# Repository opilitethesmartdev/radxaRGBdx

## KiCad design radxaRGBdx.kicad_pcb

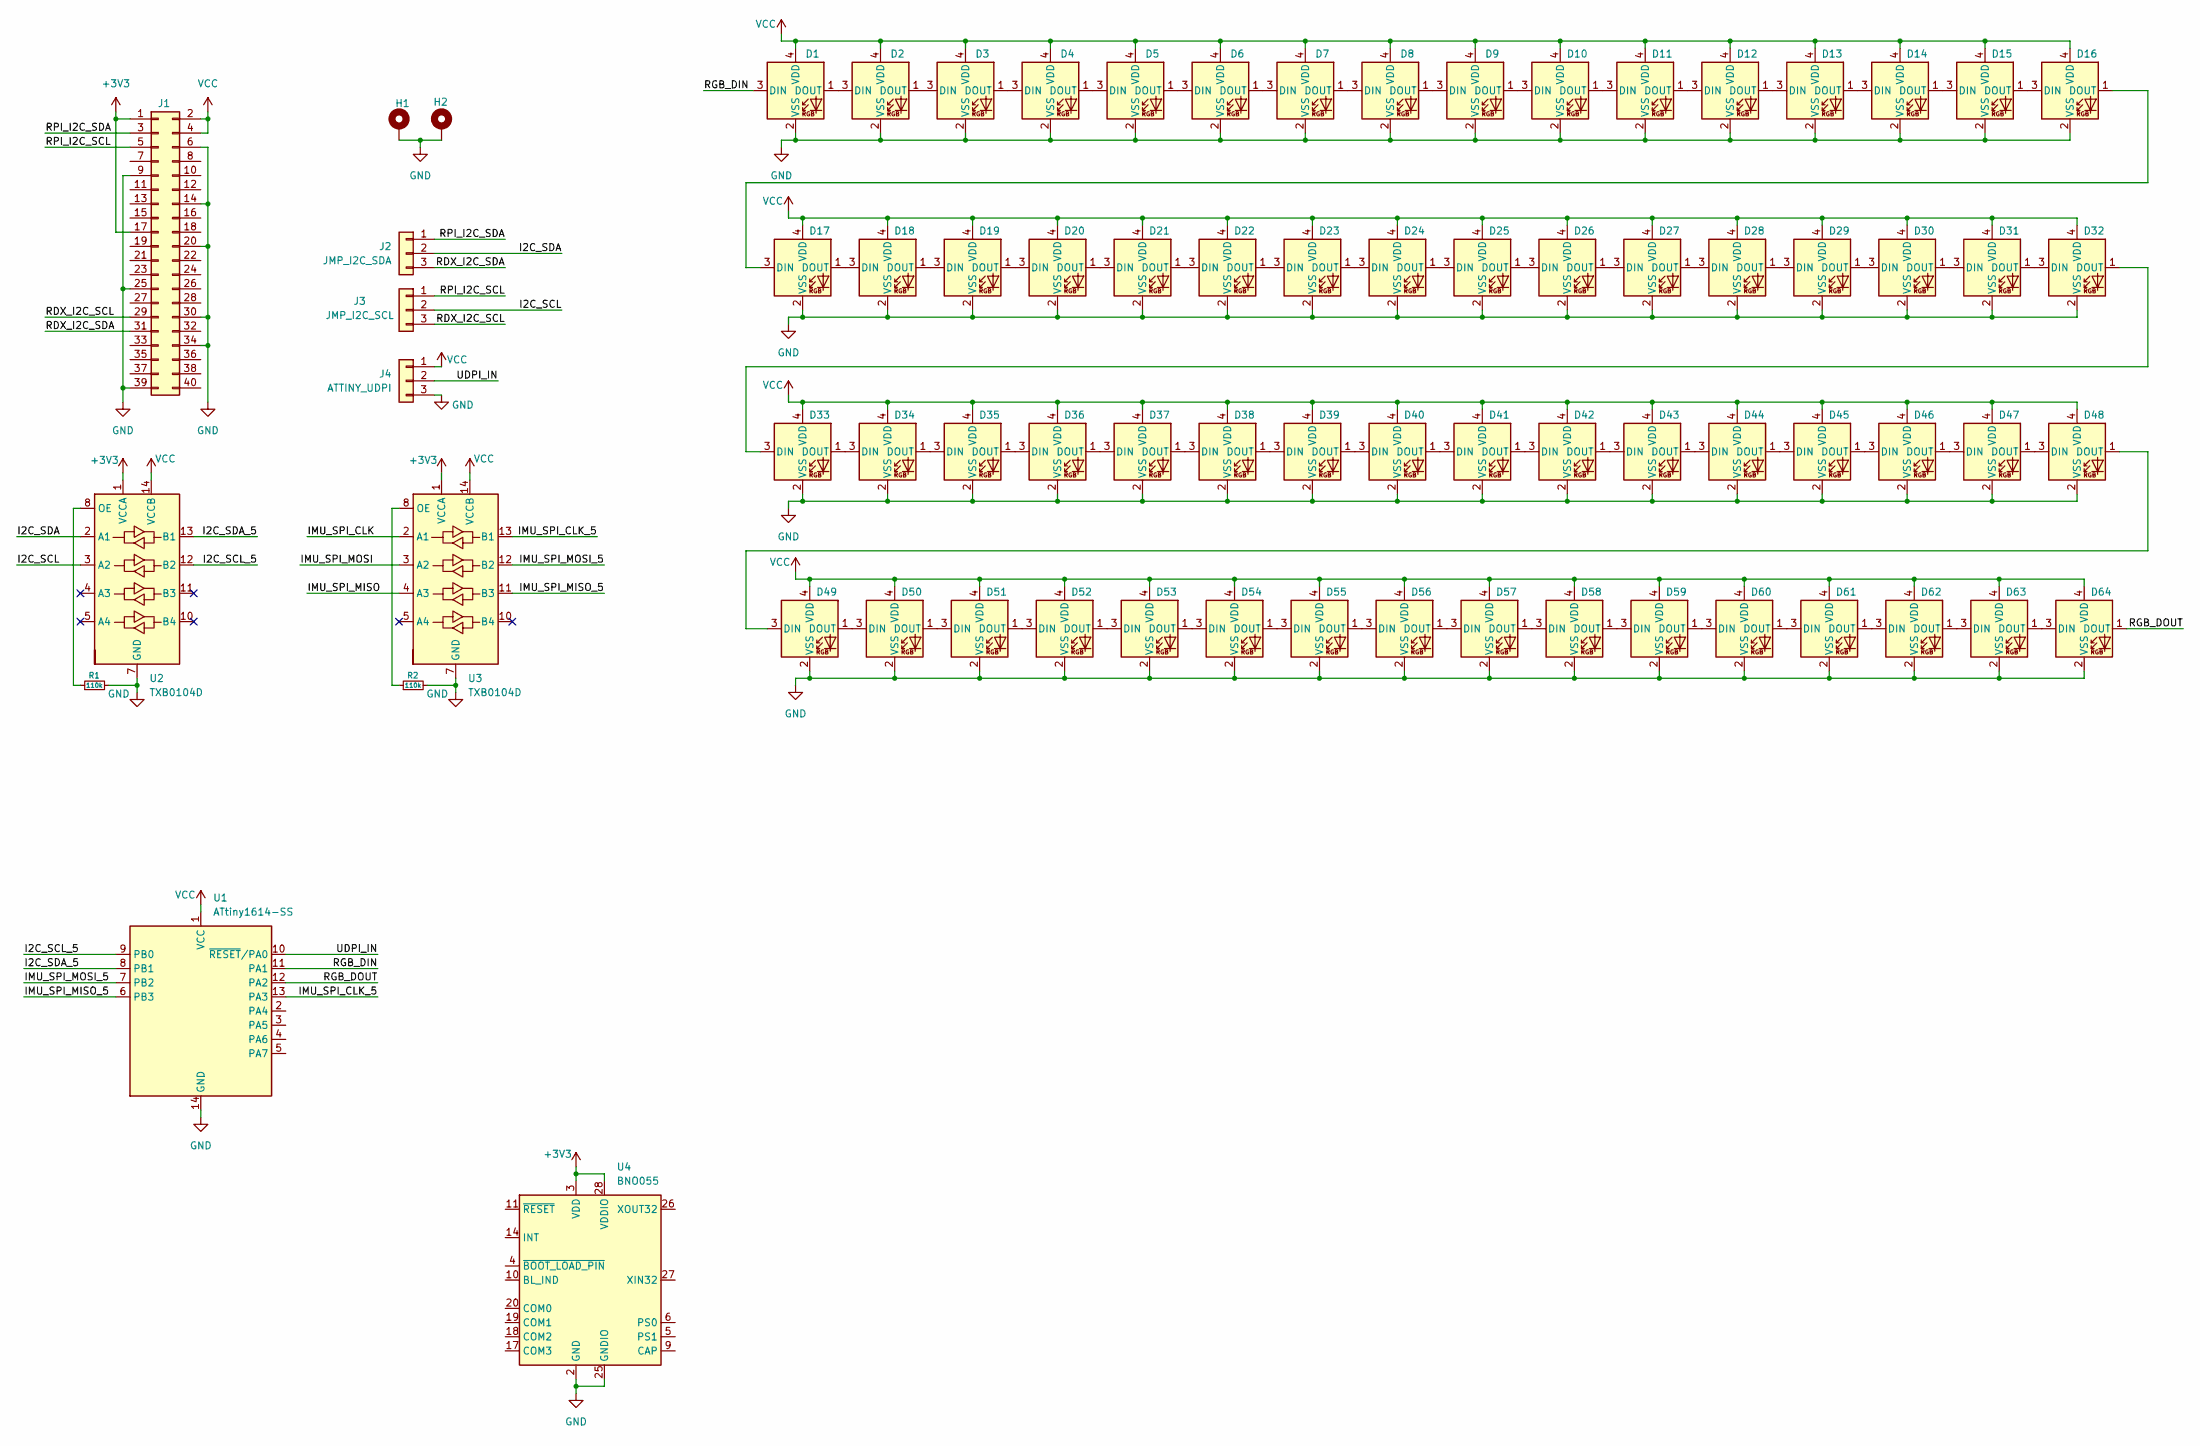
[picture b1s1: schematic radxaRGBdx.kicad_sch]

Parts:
D1, D2, D3, D4, D5, D6, D7, D8, D9, D10, D11, D12, D13, D14, D15, D16, D17, D18, D19, D20, D21, D22, D23, D24, D25, D26, D27, D28, D29, D30, D31, D32, D33, D34, D35, D36, D37, D38, D39, D40, D41, D42, D43, D44, D45, D46, D47, D48, D49, D50, D51, D52, D53, D54, D55, D56, D57, D58, D59, D60, D61, D62, D63, D64: WS2812B-2020; LED_WS2812B-2020_PLCC4_2.0x2.0mm
H1, H2: MountingHole_Pad; MountingHole_3.2mm_M3_DIN965_Pad
J1: Conn_02x20_Odd_Even; PinSocket_2x20_P2.54mm_Vertical
J2: JMP_I2C_SDA; PinHeader_1x03_P1.27mm_Vertical
J3: JMP_I2C_SCL; PinHeader_1x03_P1.27mm_Vertical
J4: ATTINY_UDPI; PinHeader_1x03_P2.54mm_Vertical
R1, R2: 110k; R_1206_3216Metric_Pad1.42x1.75mm_HandSolder
U1: ATtiny1614-SS; SOIC-14_3.9x8.7mm_P1.27mm
U2, U3: TXB0104D; SOIC-14_3.9x8.7mm_P1.27mm
U4: BNO055; LGA-28_5.2x3.8mm_P0.5mm

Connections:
+3V3: J1.1, J1.17, U2.1 (VCCA), U3.1 (VCCA), U4.3 (VDD), U4.28 (VDDIO)
/I2C_SCL: J3.2, U2.3 (A2)
/I2C_SCL_5: U1.9 (PB0), U2.12 (B2)
/I2C_SDA: J2.2, U2.2 (A1)
/I2C_SDA_5: U1.8 (PB1), U2.13 (B1)
/IMU_SPI_CLK: U3.2 (A1)
/IMU_SPI_CLK_5: U1.13 (PA3), U3.13 (B1)
/IMU_SPI_MISO: U3.4 (A3)
/IMU_SPI_MISO_5: U1.6 (PB3), U3.11 (B3)
/IMU_SPI_MOSI: U3.3 (A2)
/IMU_SPI_MOSI_5: U1.7 (PB2), U3.12 (B2)
/RDX_I2C_SCL: J1.29, J3.3
/RDX_I2C_SDA: J1.31, J2.3
/RGB_DIN: D1.3 (DIN), U1.11 (PA1)
/RGB_DOUT: D64.1 (DOUT), U1.12 (PA2)
/RPI_I2C_SCL: J1.5, J3.1
/RPI_I2C_SDA: J1.3, J2.1
/UDPI_IN: J4.2, U1.10 (~RESET/PA0)
GND: D1.2 (VSS), D2.2 (VSS), D3.2 (VSS), D4.2 (VSS), D5.2 (VSS), D6.2 (VSS), D7.2 (VSS), D8.2 (VSS), D9.2 (VSS), D10.2 (VSS), D11.2 (VSS), D12.2 (VSS), D13.2 (VSS), D14.2 (VSS), D15.2 (VSS), D16.2 (VSS), D17.2 (VSS), D18.2 (VSS), D19.2 (VSS), D20.2 (VSS), D21.2 (VSS), D22.2 (VSS), D23.2 (VSS), D24.2 (VSS), D25.2 (VSS), D26.2 (VSS), D27.2 (VSS), D28.2 (VSS), D29.2 (VSS), D30.2 (VSS), D31.2 (VSS), D32.2 (VSS), D33.2 (VSS), D34.2 (VSS), D35.2 (VSS), D36.2 (VSS), D37.2 (VSS), D38.2 (VSS), D39.2 (VSS), D40.2 (VSS), D41.2 (VSS), D42.2 (VSS), D43.2 (VSS), D44.2 (VSS), D45.2 (VSS), D46.2 (VSS), D47.2 (VSS), D48.2 (VSS), D49.2 (VSS), D50.2 (VSS), D51.2 (VSS), D52.2 (VSS), D53.2 (VSS), D54.2 (VSS), D55.2 (VSS), D56.2 (VSS), D57.2 (VSS), D58.2 (VSS), D59.2 (VSS), D60.2 (VSS), D61.2 (VSS), D62.2 (VSS), D63.2 (VSS), D64.2 (VSS), H1.1 (1_1), H2.1 (1_1), J1.6, J1.9, J1.14, J1.20, J1.25, J1.30, J1.34, J1.39, J4.3, R1.2, R2.2, U1.14 (GND), U2.7 (GND), U3.7 (GND), U4.2 (GND), U4.25 (GNDIO)
unnamed: D1.1 (DOUT), D2.3 (DIN)
unnamed: D2.1 (DOUT), D3.3 (DIN)
unnamed: D3.1 (DOUT), D4.3 (DIN)
unnamed: D4.1 (DOUT), D5.3 (DIN)
unnamed: D5.1 (DOUT), D6.3 (DIN)
unnamed: D6.1 (DOUT), D7.3 (DIN)
unnamed: D7.1 (DOUT), D8.3 (DIN)
unnamed: D8.1 (DOUT), D9.3 (DIN)
unnamed: D9.1 (DOUT), D10.3 (DIN)
unnamed: D10.1 (DOUT), D11.3 (DIN)
unnamed: D11.1 (DOUT), D12.3 (DIN)
unnamed: D12.1 (DOUT), D13.3 (DIN)
unnamed: D13.1 (DOUT), D14.3 (DIN)
unnamed: D14.1 (DOUT), D15.3 (DIN)
unnamed: D15.1 (DOUT), D16.3 (DIN)
unnamed: D16.1 (DOUT), D17.3 (DIN)
unnamed: D17.1 (DOUT), D18.3 (DIN)
unnamed: D18.1 (DOUT), D19.3 (DIN)
unnamed: D19.1 (DOUT), D20.3 (DIN)
unnamed: D20.1 (DOUT), D21.3 (DIN)
unnamed: D21.1 (DOUT), D22.3 (DIN)
unnamed: D22.1 (DOUT), D23.3 (DIN)
unnamed: D23.1 (DOUT), D24.3 (DIN)
unnamed: D24.1 (DOUT), D25.3 (DIN)
unnamed: D25.1 (DOUT), D26.3 (DIN)
unnamed: D26.1 (DOUT), D27.3 (DIN)
unnamed: D27.1 (DOUT), D28.3 (DIN)
unnamed: D28.1 (DOUT), D29.3 (DIN)
unnamed: D29.1 (DOUT), D30.3 (DIN)
unnamed: D30.1 (DOUT), D31.3 (DIN)
unnamed: D31.1 (DOUT), D32.3 (DIN)
unnamed: D32.1 (DOUT), D33.3 (DIN)
unnamed: D33.1 (DOUT), D34.3 (DIN)
unnamed: D34.1 (DOUT), D35.3 (DIN)
unnamed: D35.1 (DOUT), D36.3 (DIN)
unnamed: D36.1 (DOUT), D37.3 (DIN)
unnamed: D37.1 (DOUT), D38.3 (DIN)
unnamed: D38.1 (DOUT), D39.3 (DIN)
unnamed: D39.1 (DOUT), D40.3 (DIN)
unnamed: D40.1 (DOUT), D41.3 (DIN)
unnamed: D41.1 (DOUT), D42.3 (DIN)
unnamed: D42.1 (DOUT), D43.3 (DIN)
unnamed: D43.1 (DOUT), D44.3 (DIN)
unnamed: D44.1 (DOUT), D45.3 (DIN)
unnamed: D45.1 (DOUT), D46.3 (DIN)
unnamed: D46.1 (DOUT), D47.3 (DIN)
unnamed: D47.1 (DOUT), D48.3 (DIN)
unnamed: D48.1 (DOUT), D49.3 (DIN)
unnamed: D49.1 (DOUT), D50.3 (DIN)
unnamed: D50.1 (DOUT), D51.3 (DIN)
unnamed: D51.1 (DOUT), D52.3 (DIN)
unnamed: D52.1 (DOUT), D53.3 (DIN)
unnamed: D53.1 (DOUT), D54.3 (DIN)
unnamed: D54.1 (DOUT), D55.3 (DIN)
unnamed: D55.1 (DOUT), D56.3 (DIN)
unnamed: D56.1 (DOUT), D57.3 (DIN)
unnamed: D57.1 (DOUT), D58.3 (DIN)
unnamed: D58.1 (DOUT), D59.3 (DIN)
unnamed: D59.1 (DOUT), D60.3 (DIN)
unnamed: D60.1 (DOUT), D61.3 (DIN)
unnamed: D61.1 (DOUT), D62.3 (DIN)
unnamed: D62.1 (DOUT), D63.3 (DIN)
unnamed: D63.1 (DOUT), D64.3 (DIN)
unnamed: R1.1, U2.8 (OE)
unnamed: R2.1, U3.8 (OE)
VCC: D1.4 (VDD), D2.4 (VDD), D3.4 (VDD), D4.4 (VDD), D5.4 (VDD), D6.4 (VDD), D7.4 (VDD), D8.4 (VDD), D9.4 (VDD), D10.4 (VDD), D11.4 (VDD), D12.4 (VDD), D13.4 (VDD), D14.4 (VDD), D15.4 (VDD), D16.4 (VDD), D17.4 (VDD), D18.4 (VDD), D19.4 (VDD), D20.4 (VDD), D21.4 (VDD), D22.4 (VDD), D23.4 (VDD), D24.4 (VDD), D25.4 (VDD), D26.4 (VDD), D27.4 (VDD), D28.4 (VDD), D29.4 (VDD), D30.4 (VDD), D31.4 (VDD), D32.4 (VDD), D33.4 (VDD), D34.4 (VDD), D35.4 (VDD), D36.4 (VDD), D37.4 (VDD), D38.4 (VDD), D39.4 (VDD), D40.4 (VDD), D41.4 (VDD), D42.4 (VDD), D43.4 (VDD), D44.4 (VDD), D45.4 (VDD), D46.4 (VDD), D47.4 (VDD), D48.4 (VDD), D49.4 (VDD), D50.4 (VDD), D51.4 (VDD), D52.4 (VDD), D53.4 (VDD), D54.4 (VDD), D55.4 (VDD), D56.4 (VDD), D57.4 (VDD), D58.4 (VDD), D59.4 (VDD), D60.4 (VDD), D61.4 (VDD), D62.4 (VDD), D63.4 (VDD), D64.4 (VDD), J1.2, J1.4, J4.1, U1.1 (VCC), U2.14 (VCCB), U3.14 (VCCB)

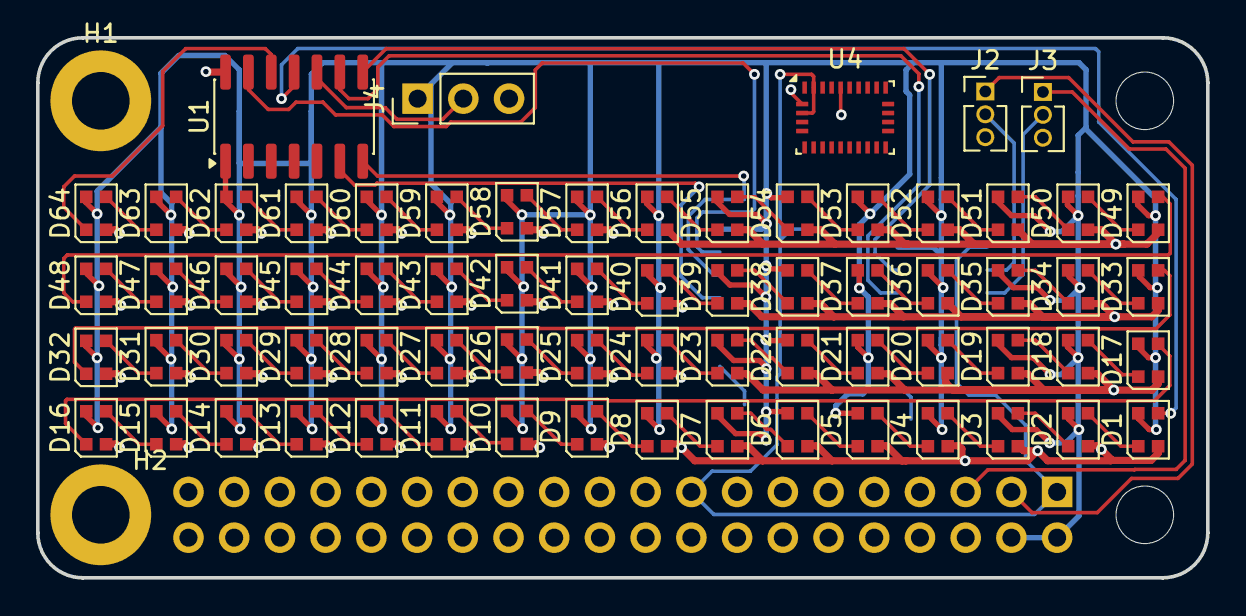
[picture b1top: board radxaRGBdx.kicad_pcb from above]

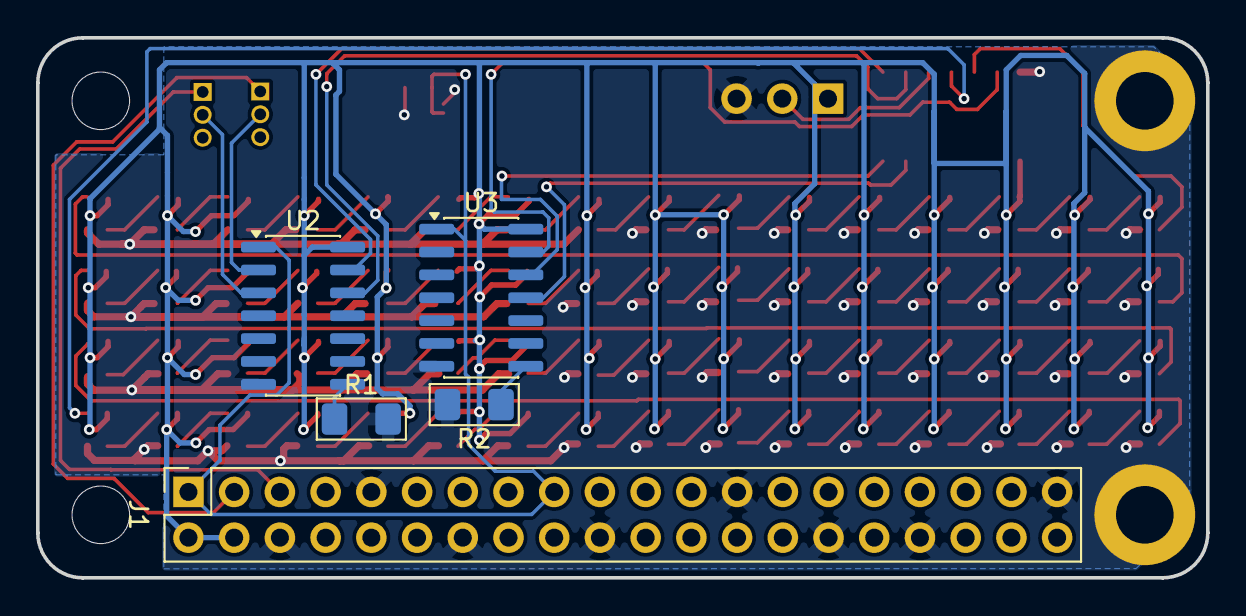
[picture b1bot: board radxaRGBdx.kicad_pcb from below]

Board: 2 copper layers, 65.0 x 30.0 mm, 76 parts (5 on the bottom side), 82 nets.
